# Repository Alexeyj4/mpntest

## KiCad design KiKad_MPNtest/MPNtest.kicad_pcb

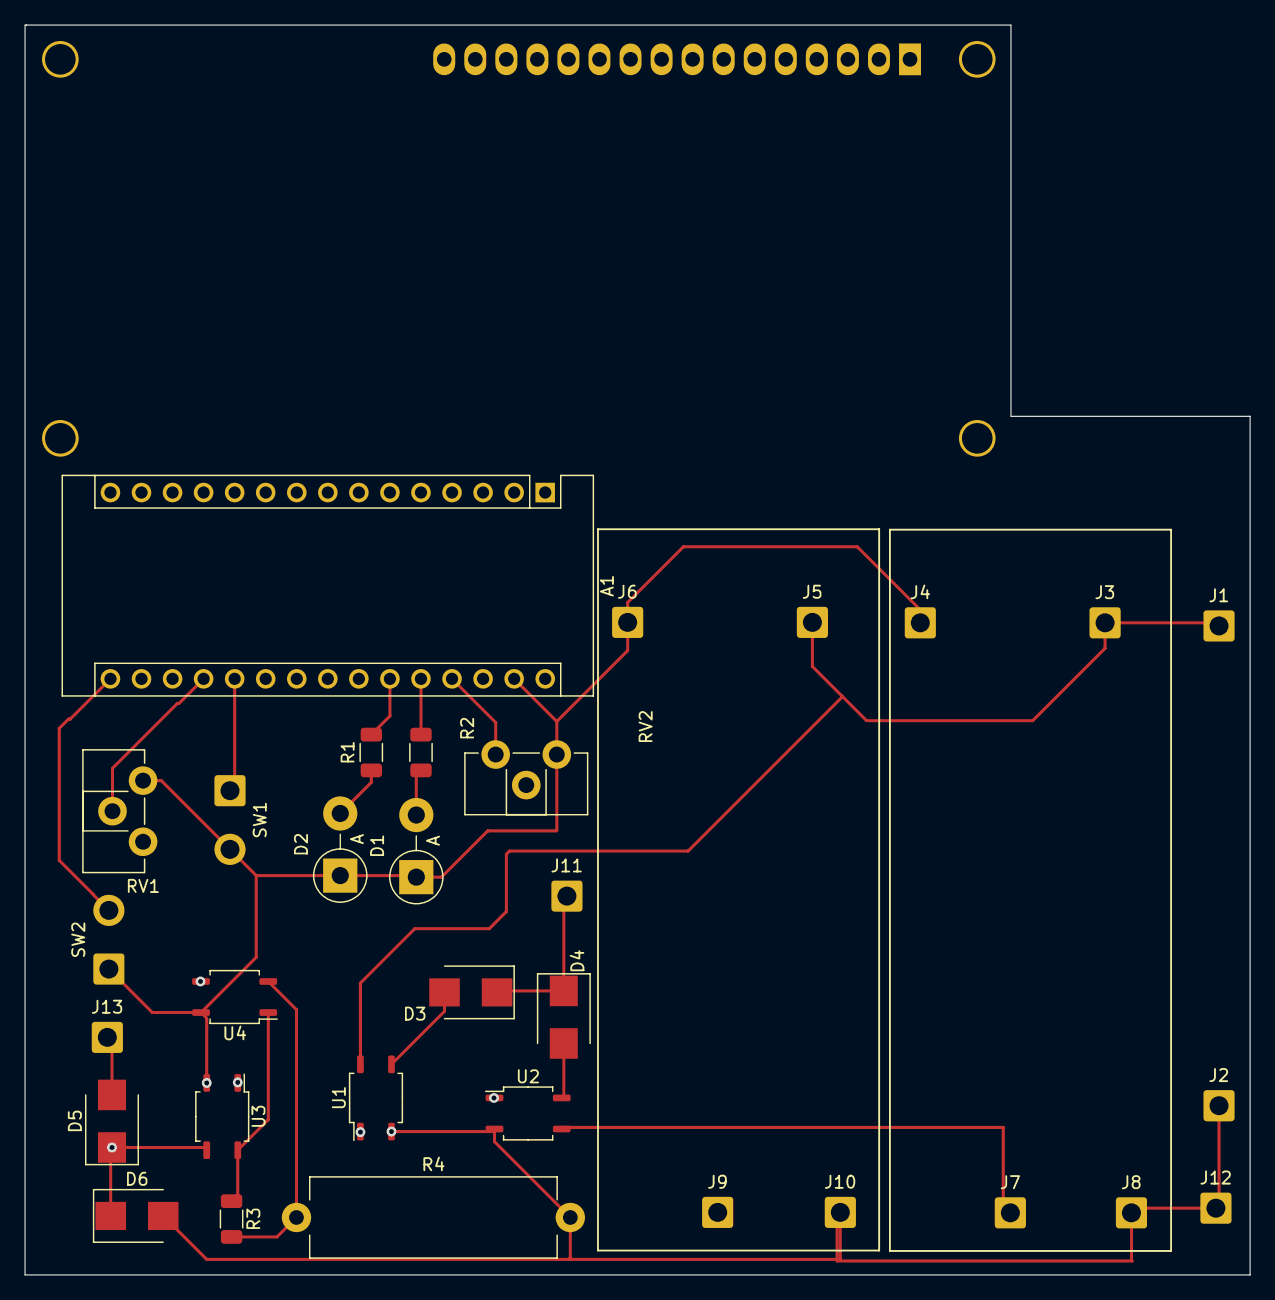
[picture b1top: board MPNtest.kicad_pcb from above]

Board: 6 copper layers, 100.2 x 102.2 mm, 33 parts (1 on the bottom side), 30 nets.

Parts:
A1: Arduino_Nano_v2.x; Arduino_Nano
D1: green(ok); D_5W_P5.08mm_Vertical_AnodeUp
D2: red(not ok); D_5W_P5.08mm_Vertical_AnodeUp
D3, D4, D5: 10BQ060; D_SMB
D6: 1N4746A (18V) x20pcs; D_SMB
DS1: WC1602A
J1: MeanWell +48V out; SolderWire-0.75sqmm_1x01_D1.25mm_OD2.3mm
J2: MeanWell GND out; SolderWire-0.75sqmm_1x01_D1.25mm_OD2.3mm
J3: MP55x9V +48V in; SolderWire-0.75sqmm_1x01_D1.25mm_OD2.3mm
J4: MP55x9V GND in; SolderWire-0.75sqmm_1x01_D1.25mm_OD2.3mm
J5: MP55xVDD +48V in; SolderWire-0.75sqmm_1x01_D1.25mm_OD2.3mm
J6: MP55xVDD GND in; SolderWire-0.75sqmm_1x01_D1.25mm_OD2.3mm
J7: MP55x9V +9V out; SolderWire-0.75sqmm_1x01_D1.25mm_OD2.3mm
J8: MP55x9V GND out; SolderWire-0.75sqmm_1x01_D1.25mm_OD2.3mm
J9: MP55xVDD +9V out; SolderWire-0.75sqmm_1x01_D1.25mm_OD2.3mm
J10: MP55xVDD GND out; SolderWire-0.75sqmm_1x01_D1.25mm_OD2.3mm
J11: MPN_test +Vin; SolderWire-0.75sqmm_1x01_D1.25mm_OD2.3mm
J12: MPN_test GND; SolderWire-0.75sqmm_1x01_D1.25mm_OD2.3mm
J13: MPN_test +Vout; SolderWire-0.75sqmm_1x01_D1.25mm_OD2.3mm
R1, R2: 3 кОм; R_1206_3216Metric
R3: 2 Ом; R_1206_3216Metric
R4: 100 Ом 2Вт; R_Axial_Power_L20.0mm_W6.4mm_P22.40mm
RV1: 22 кОм Uout_meas_cal; Potentiometer_ACP_CA9-H2,5_Horizontal
RV2: 2,2 кОм LCD_contrast; Potentiometer_ACP_CA9-H2,5_Horizontal
SW1: 6.3V / 5V switch; SolderWire-0.75sqmm_1x02_P4.8mm_D1.25mm_OD2.3mm
SW2: Start; SolderWire-0.75sqmm_1x02_P4.8mm_D1.25mm_OD2.3mm
U1, U2, U3, U4: CPC1030N; SOP-4_3.8x4.1mm_P2.54mm

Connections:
/HV_on: A1.24 (A5), U1.1
/LCD_D4: A1.12 (D9), DS1.11 (D4)
/LCD_D5: A1.13 (D10), DS1.12 (D5)
/LCD_D6: A1.14 (D11), DS1.13 (D6)
/LCD_D7: A1.15 (D12), DS1.14 (D7)
/LCD_E: A1.11 (D8), DS1.6 (E)
/LCD_RS: A1.10 (D7), DS1.4 (RS)
/LV_on: A1.23 (A4), U2.1
/VDD: A1.30 (VIN), J9.1
/load_on: A1.21 (A2), U3.1
/load_sens: A1.22 (A3), U4.3
GND: A1.4 (GND), A1.29 (GND), D1.1 (K), D2.1 (K), D6.2 (A), DS1.1 (VSS), DS1.5 (R/W), DS1.16 (LED(-)), J2.1, J4.1, J6.1, J8.1, J10.1, J12.1, R4.2, RV1.3, RV2.1, SW1.2 (B), SW2.1, U1.2, U2.2, U3.2, U4.4
unnamed: A1.16 (D13), SW2.2
unnamed: A1.19 (A0), RV1.2
unnamed: A1.20 (A1), SW1.1 (A)
unnamed: A1.25 (A6), R1.2
unnamed: A1.26 (A7), R2.2
unnamed: A1.27 (+5V), DS1.2 (VDD), DS1.15 (LED(+)), RV2.3
unnamed: D1.2 (A), R2.1
unnamed: D2.2 (A), R1.1
unnamed: D3.1 (K), D4.1 (K), J11.1
unnamed: D3.2 (A), U1.3
unnamed: D4.2 (A), U2.4
unnamed: D5.1 (K), D6.1 (K), RV1.1, U3.3
unnamed: D5.2 (A), J13.1
unnamed: DS1.3 (VO), RV2.2
unnamed: J1.1, J3.1, J5.1, U1.4
unnamed: J7.1, U2.3
unnamed: R3.1, U3.4, U4.1
unnamed: R3.2, R4.1, U4.2

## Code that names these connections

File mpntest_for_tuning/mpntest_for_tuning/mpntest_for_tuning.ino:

//define MPU pins
#define LCD_RS 7
#define LCD_E 8
#define LCD_D4 9
#define LCD_D5 10
#define LCD_D6 11
#define LCD_D7 12

#define Uout_meas A0 
#define U_sw 15
#define start_sw 4
#define red_led 3
#define green_led 2

#define load_on A2
#define load_sens A3
#define LV_on A4  //LV=10V
#define HV_on A5  //HV=48V

//calibrating constants for 6.3v- and 5v- mode:
//"norm" - measured
const int v_overvoltage =1;

int MODE=6; //6.3V=6 5V=5
int Vmin=0; //temp for compare
int Vmax=0; //temp for compare
bool bad=true; //bad flag
bool dbg=true; //dbg mode flag (for developers)

//min6.0 max 6.5:
const int v6_max_LV_open =518;//norm=504/6.32
const int v6_min_LV_open =478;//norm=504/6.32
const int v6_max_LV_load =509;//norm=485/6.19 
const int v6_min_LV_load =470;//norm=485/6.19
//min6.0 max 6.6:
const int v6_max_HV_open =525;//norm=512/6.44
const int v6_min_HV_open =477;//norm=512/6.44
const int v6_max_HV_load =519;//norm=504/6.41
const int v6_min_HV_load =471;//norm=504/6.41

//min4.8 max5.3:
const int v5_max_LV_open =418;//norm=407/5.15
const int v5_min_LV_open =379;//norm=407/5.15
const int v5_max_LV_load =411;//norm=398/5.13
const int v5_min_LV_load =372;//norm=398/5.13
//min4.8 max5.4:
const int v5_max_HV_open =428;//norm=415/5.24
const int v5_min_HV_open =380;//norm=415/5.24
const int v5_max_HV_load =420;//norm=404/5.20
const int v5_min_HV_load =373;//norm=404/5.20




#include <LiquidCrystal.h>  // Лобавляем необходимую библиотеку для LCD
LiquidCrystal lcd(LCD_RS, LCD_E, LCD_D4, LCD_D5, LCD_D6, LCD_D7); // (RS, E, DB4, DB5, DB6, DB7) //physical pin

void setup() {
  // put your setup code here, to run once:

  digitalWrite(LV_on, LOW); //set 48v off
  digitalWrite(HV_on, LOW); //ste 10v off

  analogReference(INTERNAL);
  Serial.begin(115200);

  pinMode(red_led, OUTPUT);
  pinMode(green_led, OUTPUT);
  pinMode(Uout_meas, INPUT);
  pinMode(U_sw, INPUT_PULLUP);
  pinMode(start_sw, INPUT_PULLUP);

  pinMode(load_on, OUTPUT);
  pinMode(load_sens, INPUT_PULLUP);
  pinMode(LV_on, OUTPUT);
  pinMode(HV_on, OUTPUT);


  lcd.begin(16, 2);           // Задаем размерность экрана
  lcd.setCursor(0, 0);        // Устанавливаем курсор в начало 1 строки
  lcd.print("test LCD");      // Выводим текст 
  lcd.setCursor(0, 1);        // Устанавливаем курсор в начало 2 строки
  lcd.print("mpntest");       // Выводим текст 

  Serial.println("");
  Serial.println("***********Start************");
  analogRead(Uout_meas);//first read for reduce error

  startscreen();


}

void loop() {
  // put your main code here, to run repeatedly:

  if(MODE==5 && digitalRead(U_sw)==LOW)//mode switched up=6.3V
  {
    MODE=6;
    startscreen();
  }

  if(MODE==6 && digitalRead(U_sw)==HIGH)//mode switched down=5V
  {
    MODE=5;
    startscreen();
  }


  //if(digitalRead(start_sw)==LOW) test(); //start btn pressed
  test();



}

void test()
{ 

  bad=false;
  
  //blink leds:
  digitalWrite(red_led, LOW);
  digitalWrite(green_led, LOW);
  delay(10);
  digitalWrite(red_led, HIGH);
  digitalWrite(green_led, HIGH);
  delay(10);
  digitalWrite(red_led, LOW);
  digitalWrite(green_led, LOW);

//*********test 1*******
  //10v open (LV):
  if (MODE==6) {Vmin=v6_min_LV_open; Vmax=v6_max_LV_open;}
  if (MODE==5) {Vmin=v5_min_LV_open; Vmax=v5_max_LV_open;}
  digitalWrite(HV_on, LOW); //set 48v off
  digitalWrite(LV_on, HIGH); //ste 10v on
  if(overvoltage_test()==true)return;
  digitalWrite(load_on, LOW); //set load off
  delay(200);  

  lcd.begin(16, 2);           // Задаем размерность экрана
  lcd.setCursor(0, 0);        // Устанавливаем курсор в начало 1 строки
  
  if((Vmin < analogRead(Uout_meas)) && (analogRead(Uout_meas) < Vmax)) lcd.print("10-OK"); else {lcd.print("10-BAD"); bad=true;};   
  Serial.println(""); 
  Serial.print("10v open Uout_meas: "); Serial.print(Vmin); Serial.print(" < "); Serial.print(analogRead(Uout_meas)); Serial.print(" < "); Serial.print(Vmax); Serial.print(" | load=");Serial.println(digitalRead(load_sens));

  if (dbg==true) delay(4000);
  
  //if(digitalRead(load_sens)==0) {message("LOAD FAIL!");return;}

  digitalWrite(LV_on, LOW); //set 10v off
  digitalWrite(HV_on, LOW); //set 48v on  
  digitalWrite(load_on, LOW); //set load off
  delay(300);

//*********test 2*******
  //10v load (LV):
  if (MODE==6) {Vmin=v6_min_LV_load; Vmax=v6_max_LV_load;}
  if (MODE==5) {Vmin=v5_min_LV_load; Vmax=v5_max_LV_load;}
  digitalWrite(HV_on, LOW); //set 48v off
  digitalWrite(LV_on, HIGH); //ste 10v on
  if(overvoltage_test()==true)return;
  digitalWrite(load_on, HIGH); //set load on
  delay(200);

  lcd.setCursor(8, 0);        // Устанавливаем курсор в середину 1 строки
    
  if((Vmin < analogRead(Uout_meas)) && (analogRead(Uout_meas) < Vmax)) lcd.print("10L-OK"); else {lcd.print("10-BAD"); bad=true;};   
  Serial.print("10v load Uout_meas: "); Serial.print(Vmin); Serial.print(" < "); Serial.print(analogRead(Uout_meas)); Serial.print(" < "); Serial.print(Vmax); Serial.print(" | load=");Serial.println(digitalRead(load_sens)); 

  if (dbg==true) delay(4000);

  //if(digitalRead(load_sens)==1) {message("LOAD FAIL!");return;}
  
  digitalWrite(LV_on, LOW); //set 10v off
  digitalWrite(HV_on, LOW); //set 48v on 
  digitalWrite(load_on, LOW); //set load off
  delay(300);

//*********test 3*******
  //48v open (HV):
  if (MODE==6) {Vmin=v6_min_HV_open; Vmax=v6_max_HV_open;}
  if (MODE==5) {Vmin=v5_min_HV_open; Vmax=v5_max_HV_open;}  
  digitalWrite(LV_on, LOW); //set 10v off
  digitalWrite(HV_on, HIGH); //set 48v on
  if(overvoltage_test()==true)return;
  digitalWrite(load_on, LOW); //set load off
  delay(200);  

  lcd.setCursor(0, 2);        // Устанавливаем курсор в начало 2 строки

  if((Vmin < analogRead(Uout_meas)) && (analogRead(Uout_meas) < Vmax)) lcd.print("48-OK"); else {lcd.print("48-BAD"); bad=true;};   
  Serial.print("48v open Uout_meas: "); Serial.print(""); Serial.print(Vmin); Serial.print(" < "); Serial.print(analogRead(Uout_meas)); Serial.print(" < "); Serial.print(Vmax); Serial.print(" | load=");Serial.println(digitalRead(load_sens)); 

  if (dbg==true) delay(4000);

  //if(digitalRead(load_sens)==0) {message("LOAD FAIL!");return;}
  
  digitalWrite(LV_on, LOW); //set 10v off
  digitalWrite(HV_on, LOW); //set 48v on    
  digitalWrite(load_on, LOW); //set load off
  delay(300);

//*********test 4*******
  //48v load (HV):
  if (MODE==6) {Vmin=v6_min_HV_load; Vmax=v6_max_HV_load;}
  if (MODE==5) {Vmin=v5_min_HV_load; Vmax=v5_max_HV_load;}  
  digitalWrite(LV_on, LOW); //set 10v off
  digitalWrite(HV_on, HIGH); //set 48v on
  if(overvoltage_test()==true)return;
  digitalWrite(load_on, HIGH); //set load on
  delay(200);  

  lcd.setCursor(8, 2);        // Устанавливаем курсор в середину 2 строки

  if((Vmin < analogRead(Uout_meas)) && (analogRead(Uout_meas) < Vmax)) lcd.print("48L-OK"); else {lcd.print("48-BAD"); bad=true;};  
  Serial.print("48v load Uout_meas: "); Serial.print(""); Serial.print(Vmin); Serial.print(" < "); Serial.print(analogRead(Uout_meas)); Serial.print(" < "); Serial.print(Vmax); Serial.print(" | load=");Serial.println(digitalRead(load_sens)); 

  if (dbg==true) delay(4000);

  //if(digitalRead(load_sens)==1) {message("LOAD FAIL!");return;}
  
  digitalWrite(LV_on, LOW); //set 10v off
  digitalWrite(HV_on, LOW); //set 48v on  
  digitalWrite(load_on, LOW); //set load off
  delay(300);




  if (bad==true) {    //"not ok" led 
    digitalWrite(red_led, HIGH);
    digitalWrite(green_led, LOW);
  }
  if (bad==false) {   //"ok" led
    digitalWrite(red_led, LOW);
    digitalWrite(green_led, HIGH);
  }  

  
}


void startscreen()
{
  if(digitalRead(U_sw)==LOW) //switch up=6.3V
  {
  lcd.begin(16, 2);           // Задаем размерность экрана
  lcd.setCursor(0, 0);        // Устанавливаем курсор в начало 1 строки
  lcd.print("Connect MPN 6.3V");      // Выводим текст 
  lcd.setCursor(0, 1);        // Устанавливаем курсор в начало 2 строки
  lcd.print("Press Start");       // Выводим текст 
  }

  if(digitalRead(U_sw)==HIGH) //switch down=5V
  {
  lcd.begin(16, 2);                // Задаем размерность экрана
  lcd.setCursor(0, 0);            // Устанавливаем курсор в начало 1 строки
  lcd.print("Connect MPN 5V");    // Выводим текст 
  lcd.setCursor(0, 1);            // Устанавливаем курсор в начало 2 строки
  lcd.print("Press Start");       // Выводим текст 
  }
}

void message(String s)
{
  lcd.begin(16, 2);           // Задаем размерность экрана
  lcd.setCursor(0, 0);        // Устанавливаем курсор в начало 1 строки
  lcd.print(s);               // Выводим текст 
}

bool overvoltage_test()
{
  if(analogRead(Uout_meas)>v6_max_HV_open)
  {
    digitalWrite(LV_on, LOW); //set 10v off
    digitalWrite(HV_on, LOW); //set 48v on  
    message("OVERVOLTAGE !!!");
    return true;
  }
  else return false;
}

   

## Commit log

2022-12-09 kicad files added
